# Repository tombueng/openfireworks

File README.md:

<div align="center">

# 🎆 OpenFireworks

**An open, DIY firework show platform — 24-channel ESP32-C3 firing nodes + a browser-based 3D show planner.**

Plan a pyromusical in realistic 3D, then fire it from a cheap, safe, fully open node.

**[▶ Open the interactive 3D viewer](https://tombueng.github.io/openfireworks/)** ·
**[▶ Open OpenFireworks Studio](https://tombueng.github.io/openfireworks/studio/)** — both run in the browser, no install

</div>

> [!WARNING]
> **Pyrotechnics are dangerous and legally regulated.** This repo is an engineering project, not a licence to
> fire. Obey local law and safety distances. On the node the **slide switch is the physical master-off**; firing
> additionally needs an explicit software arm that powers the firing rail (high-side P-FET) and enables the gate
> drivers — boot-safe disarmed by hardware pulldowns.
>
> **Status 2026-11:** the respin-3 hardware is ordered but not yet built or tested; the firmware has never run on
> a board. Do not connect live e-matches before the bench tests in
> [`docs/RESPIN3_BUILD_AND_FIRMWARE.md`](docs/RESPIN3_BUILD_AND_FIRMWARE.md) §5/§6 have passed on your own board.

---

## Gallery

<table>
<tr>
<td width="50%"><br>
<sub><b>The board</b> — 24 channels on 3.5 mm jacks, one RGB status LED per channel</sub></td>
<td width="50%"><br>
<sub><b>Underside</b> — 4 × AA holder, ESP32-C3 SuperMini, master switch</sub></td>
</tr>
<tr>
<td><br>
<sub><b>Case opened</b> — the lid flips off; the board drops into the base</sub></td>
<td><br>
<sub><b>Exploded</b> — base · board · lid with 26 clear window plugs</sub></td>
</tr>
<tr>
<td><br>
<sub><b>Top-down</b> — 74HC595 drivers + 74HC4051 continuity muxes between the jack rows</sub></td>
<td><br>
<sub><b>Opened, from above</b> — board in the base, lid inside-up with its window pockets</sub></td>
</tr>
</table>

All renders come straight from the real KiCad board (its exported 3D model) and the generated enclosure —
Blender/Cycles, script [`enclosure/blender/showcase.py`](enclosure/blender/showcase.py).

### Interactive 3D viewer

Orbit, fly and explode the real board + enclosure in the browser, with the status LEDs lighting through the
windows: **[tombueng.github.io/openfireworks](https://tombueng.github.io/openfireworks/)** (drag the *Open case*
slider).

### Node web UI

Every node serves its own HTTPS web UI (no cloud, no app): all 24 channels with plug detect, continuity and
fire state, live supply voltages, self-test and battery-under-load results, arming, single-channel fire and
cue sequences. Built mobile first for a cold night outside with gloves: big touch targets, STOP as a
full-width bar at the thumb, press-and-hold to fire, a loud "no connection" banner, a high-contrast daylight
theme and the screen kept awake.

*(Screenshot from the UI mock server with simulated data.)*

<br clear="right">

---

## What's here

| Part | Path | Status |
|---|---|---|
| **24-channel firing node v2** (PCB) | `hw/openfireworks_v2.*`, `tools/` | respin 3 done (3 independent review rounds): ERC 0/0, DRC 0 errors / 0 unconnected / parity 0, fab outputs in `export/fab_v2/`, **ordered** |
| **Enclosure** (3D-printed clamshell) | `enclosure/` | generated from the board's 3D models, fit check PASS, interactive three.js viewer; **print package** (multi-material 3MF plates, fit coupon, settings) in `enclosure/print/` |
| **Node firmware** (ESP32-C3) | `firmware/openfireworks_node_v2/` | safe boot, self-tests, arming state machine, per-channel continuity/plug detect, HTTPS web UI, cue sequences, bench tests — compiles clean, **not yet run on hardware** |
| **OpenFireworks Studio** (3D planner/sim/console) | `web/studio/` | self-contained WebGL app: aerial + ground effects, cinematic cameras, sequencer, music, HD/4K recording, demo show |
| **Docs** | `docs/` | design `docs/RESPIN3_DESIGN.md`; assembly, bring-up + firmware safety rules `docs/RESPIN3_BUILD_AND_FIRMWARE.md`; how to regenerate everything `docs/REPRODUCE.md`; BOM with MPNs `export/fab_v2/openfireworks_v2-bom-full.csv` |

This repository holds the result and the scripts that regenerate it. Not in it: datasheets (copyright of
their makers — look them up by the MPN in the BOM), sourcing data, design reviews and older versions.

## What the node measures and records

Everything below is shown live in the node's web UI and on its LEDs. Values marked *expected* are calculated
for respin 3 and still have to be confirmed on the first board.

**Before firing (disarmed, and again on every arm request)**

| what | how | resolution / limit |
|---|---|---|
| Plug in or not, per jack | 100 kΩ plug-detect resistor on the jack's switch contact, read through the mux | yes / no |
| E-match continuity, per jack | test current from 3.3 V through 100 kΩ, 2-level 74HC4051 mux, one ADC | **classes only:** OK (< 0.5 kΩ) / plug with open match / SHORT / no plug, plus the sense voltage. 1–2 Ω cannot be resolved, so a bad but conducting match reads "OK" |
| Battery, resting | VSYS divider on the ADC | V; arming refused below 4.6 V |
| Battery under load | known LED load (~0.3 A) → voltage drop → internal resistance | R_int and the **predicted fire current**; arming refused below 1.2 A |
| Firing rail dead | VFIRE divider, every mux code, with logic lines held high and LED frames running (T0) | rail must read ≈ 0 V |
| Shift-register chain intact | serial readback of the whole chain (T1) | bit-exact |
| Output-enable barrier works | readback pin on the gate drivers' enable (OE_RB), tests T2/T3 | stuck on/off detected |
| Every firing FET switches, none is stuck on | walking-one with the rail off (T5): the commanded channel must read ≈ 1.05 V | per channel |
| Node health | chip temperature, Wi-Fi clients + weakest RSSI, uptime, watchdog, firmware hash | — |

**During a pulse** (one channel at a time, hardware-timed by the RMT peripheral, ≤ 15 ms)

| what | how | effect |
|---|---|---|
| Dead short on the channel | VFIRE (lag-corrected) at 1.5 ms after the start | **abort**: channel off, rail off, logged |
| Bridge burnt through | VSYS sags ≥ 8 % when the match conducts and recovers to ≥ 97 % when it opens | pulse **ends early**; the actual pulse length is recorded |
| Second barrier really switched | OE_RB must go 0 within 10 µs and back to 1 after the pulse | otherwise FAULT |
| Supply collapse | VSYS < 3.5 V for > 2 ms outside a pulse | disarm |

**After firing**

| what | where |
|---|---|
| Per channel: fired, result (ok / short abort / failed), pulse length, time since | channel tile in the web UI; LED dim white = fired, red blink = aborted |
| Continuity after the shot (open = burnt match) | next scan, disarmed |
| Event log: arm/disarm, every pulse with its result, skipped or late cues, faults, refused requests | web UI + USB console, **last 25 events, in RAM only** |

Not recorded: there is no persistent log, no export of a firing report, no time stamp beyond the node's
uptime (no real-time clock; the phone can set a birth time once), and no per-channel current measurement.

## Hardware limits (respin 3)

- **Not tested yet.** The board is ordered, the firmware has never run on it. Everything here is design intent.
- **One channel at a time.** Pulses are sequential (≈ 6.4 ms per channel incl. the LED update); cues must be
  ≥ 20 ms apart. Two effects cannot fire in the very same millisecond on one node.
- **Fire current comes straight from 4 × AA cells** (internal resistance ≈ 0.6–1.2 Ω): enough for standard
  e-matches, not for many in parallel on one channel. Alkaline cells lose a lot in the cold — **use lithium AA
  below 0 °C**. Only AA cells, never 14500 Li-ion (16.8 V destroys the board). Supply range 4.0–7.5 V.
- **Pulse length** ≤ 15 ms (≤ 8 ms when the battery rests below ~5 V, the hold-up must carry the MCU).
- **Jacks:** PJ-320A contacts are rated 0.5 A continuous; the short fire pulses (several A × ms) are fine by
  design but must pass the 50-pulse endurance test (`docs/RESPIN3_BUILD_AND_FIRMWARE.md` §5) before a show.
- **Continuity is a go/no-go test**, not an ohmmeter (see above); a shorted plug pulls the shared rail, so one
  short reads as "short" on every plugged channel and is reported as one fault.
- **Protection:** PPTC (1.5 A hold) on the battery, TVS on every output. The PPTC alone is too slow for a
  sustained short — the firmware's 1.5 ms short abort is the real protection.
- **No hardware arm key.** Both arm barriers are MCU pins with hardware pulldowns; web arming needs a press on
  the module's BOOT button within 30 s. USB is unauthenticated full control — no laptop on the node during a show.
- **Radio:** one node, its own hidden Wi-Fi access point (2.4 GHz, external antenna), range of a phone hotspot.
  No multi-node link, no time sync between nodes, no LoRa yet.
- **Cue lists live in RAM** (≤ 3600 s, lost on reset); the node auto-disarms after 30 min armed.
- **Weather:** the printed case is splash-resistant at best and the jacks are open. Dew: consider conformal
  coating on the bottom side for night shows.
- **No 5 V LED-rail sense** (the UI shows an estimate); LED current is capped at 0.3 A.

## The hardware node

**One board, 100 × 100 mm, 4 layers (JLCPCB standard stack-up).**

- 🧠 **ESP32-C3 SuperMini** (USB-C for programming only) · 4 × 74HC595 + 4 × 74HC4051
- 🔌 **24 low-side N-FET channels** (AO3400) on **3.5 mm jacks** (PJ-320A, with plug detect)
- 🔋 **4 × AA cells** in an on-board Keystone 2477 holder (alkaline, NiMH or lithium, 4.0–7.5 V) ·
  reverse-polarity P-FET · **PPTC** · slide switch master-off · e-matches fire straight from the cells through
  the channel FET; LDOs for 3.3 V (with hold-up capacitors) and the 5 V LED rail
- 🛡️ **Software arm with two independent barriers**, each on its own MCU pin with its own pulldown: ARM P-FET on
  the firing rail (bled to 0 V when disarmed) + gate-driver output enable (with readback); VFIRE and VBAT
  sensed by the ADC; per-channel continuity through a 2-level mux; ESD TVS on every output
- 🌈 **26 WS2812B status LEDs** (one per channel + 2 heads) on a 5 V LDO rail with a level shifter; any subset
  of channels can be populated (per-channel LED bypass jumper)
- 📡 External 2.4 GHz antenna through the enclosure wall (U.FL → SMA pigtail)
- ♻️ **Reproducible:** schematic, board, routing helpers, fab outputs, enclosure, print plates and renders are
  all generated by scripts — pipeline in [`docs/REPRODUCE.md`](docs/REPRODUCE.md)

## Enclosure

A two-part snap-fit clamshell (PETG), generated with build123d from the board's own 3D model: jack half-holes
in both halves, 26 frosted clear window plugs printed with the second extruder **beside** the lid, print-in-place
release buttons, SMA antenna port. Printing: [`enclosure/print/PRINT_SETTINGS.md`](enclosure/print/PRINT_SETTINGS.md)
(start with the fit coupon on plate 0).

## Firmware

```bash
firmware/build.sh          # bring-up
firmware/build.sh show     # show firmware
firmware/build.sh bench    # bench tests
```

See [`firmware/openfireworks_node_v2/README.md`](firmware/openfireworks_node_v2/README.md) for the safety model, the
LED colour code and the web UI.

## OpenFireworks Studio

Open `web/studio/index.html` in a modern browser (needs WebGL; three.js loads from jsDelivr), or use the hosted
copy: **[tombueng.github.io/openfireworks/studio](https://tombueng.github.io/openfireworks/studio/)**

- ▶ Show runs the demo; add effects from the library at the playhead; drag = orbit, scroll = zoom
- Cameras incl. **drone fly-through**; an **auto-director** cuts between them
- Wind drifts smoke + stars; load your own music; **record HD/4K** to a `.webm` (local only)
- Export/import shows as JSON

## Roadmap (honest)

Rig/box modelling + igniter-port mapping UI + printable setup sheets · browser-DB versioned save · monitoring
console UI + fleet management · production crypto (HMAC/AEAD) · LoRa second radio · product catalog import ·
firing-system export adapters.

## License

MIT — see [`LICENSE`](LICENSE). It covers everything in this repository: software, firmware, hardware design
files (schematic, board, fab outputs), enclosure and documentation. Third-party parts (KiCad library footprints
and 3D models, makers' datasheets, three.js loaded from a CDN) keep their own licenses.

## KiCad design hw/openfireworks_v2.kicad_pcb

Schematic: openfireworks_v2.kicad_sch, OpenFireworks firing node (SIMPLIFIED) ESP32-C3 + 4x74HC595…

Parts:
A1: ESP32-C3 SuperMini; ESP32C3_SuperMini_MINIV1; MPN ESP32-C3 SuperMini 'ESP32-C3 MINI V1' (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
BT1: 4xAA holder; BatteryHolder_Keystone_2477_4xAA; MPN Keystone 2477 (PC battery holder 4 x AA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
C1, C2, C4, C5, C7, C66: 10uF; C_0805_2012Metric; MPN 10uF 25V X5R 0805
C3, C6, C8, C10, C11, C12, C13, C14, C15, C16, C17, C18, C19, C20, C21, C22, C23, C24, C65, C71, C72, C73, C74, C75, C76: 100nF; C_0603_1608Metric; MPN 100nF 50V X7R 0603
C9, C60, C61, C70: 10nF; C_0603_1608Metric; MPN 10nF 50V X7R 0603
C62, C63, C64: 10uF; C_1206_3216Metric; MPN Samsung CL31B106KAHNNNF (10uF 25V X7R 1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
C67, C68: 470uF 10V; CP_Radial_D8.0mm_P3.50mm; MPN Nichicon UPW1A471MPD (470 uF 10 V, low 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
C69: 220nF; C_0603_1608Metric; MPN 220nF 25V X7R 0603
D1, D2, D3, D4, D5, D6, D7, D8, D9, D10, D11, D12, D13, D14, D15, D16, D17, D18, D19, D20, D21, D22, D23, D24, D49, D50: WS2812B; LED_WS2812B_PLCC4_5.0x5.0mm_P3.2mm; MPN WS2812B 5050 PLCC4 addressable RGB (5 V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
D25, D26, D27, D28, D29, D30, D31, D32, D33, D34, D35, D36, D37, D38, D39, D40, D41, D42, D43, D44, D45, D46, D47, D48, D52: ESD5Z12-AQ; D_SOD-523; MPN Diotec ESD5Z12-AQ (unidirectional ESD T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
D51: 1N5819HW; D_SOD-123; MPN Diodes Inc 1N5819HW-7-F (Schottky 40 V 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
F1: PPTC 1.5A hold; Fuse_2920_7451Metric_Pad2.10x5.45mm_HandSolder; MPN Littelfuse 2920L150DR (PPTC 1.5 A hold,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
J1, J2, J3, J4, J5, J6, J7, J8, J9, J10, J11, J12, J13, J14, J15, J16, J17, J18, J19, J20, J21, J22, J23, J24: PJ-320A; Jack_35mm_PJ320A_THT; MPN PJ-320A 3.5 mm 4-pole jack, THT 4-pin, 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
JP1: JP_D0; SolderJumper-2_P1.3mm_Open_Pad1.0x1.5mm; MPN solder bridge (PCB copper, no bought pa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
JP2: JP_D1; SolderJumper-2_P1.3mm_Open_Pad1.0x1.5mm; MPN solder bridge (PCB copper, no bought pa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
JP3: JP_D2; SolderJumper-2_P1.3mm_Open_Pad1.0x1.5mm; MPN solder bridge (PCB copper, no bought pa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
JP4: JP_D3; SolderJumper-2_P1.3mm_Open_Pad1.0x1.5mm; MPN solder bridge (PCB copper, no bought pa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
JP5: JP_D4; SolderJumper-2_P1.3mm_Open_Pad1.0x1.5mm; MPN solder bridge (PCB copper, no bought pa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
JP6: JP_D5; SolderJumper-2_P1.3mm_Open_Pad1.0x1.5mm; MPN solder bridge (PCB copper, no bought pa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
JP7: JP_D6; SolderJumper-2_P1.3mm_Open_Pad1.0x1.5mm; MPN solder bridge (PCB copper, no bought pa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
JP8: JP_D7; SolderJumper-2_P1.3mm_Open_Pad1.0x1.5mm; MPN solder bridge (PCB copper, no bought pa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
JP9: JP_D8; SolderJumper-2_P1.3mm_Open_Pad1.0x1.5mm; MPN solder bridge (PCB copper, no bought pa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
JP10: JP_D9; SolderJumper-2_P1.3mm_Open_Pad1.0x1.5mm; MPN solder bridge (PCB copper, no bought pa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
JP11: JP_D10; SolderJumper-2_P1.3mm_Open_Pad1.0x1.5mm; MPN solder bridge (PCB copper, no bought pa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
JP12: JP_D11; SolderJumper-2_P1.3mm_Open_Pad1.0x1.5mm; MPN solder bridge (PCB copper, no bought pa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
JP13: JP_D12; SolderJumper-2_P1.3mm_Open_Pad1.0x1.5mm; MPN solder bridge (PCB copper, no bought pa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
JP14: JP_D13; SolderJumper-2_P1.3mm_Open_Pad1.0x1.5mm; MPN solder bridge (PCB copper, no bought pa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
JP15: JP_D14; SolderJumper-2_P1.3mm_Open_Pad1.0x1.5mm; MPN solder bridge (PCB copper, no bought pa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
JP16: JP_D15; SolderJumper-2_P1.3mm_Open_Pad1.0x1.5mm; MPN solder bridge (PCB copper, no bought pa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
JP17: JP_D16; SolderJumper-2_P1.3mm_Open_Pad1.0x1.5mm; MPN solder bridge (PCB copper, no bought pa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
JP18: JP_D17; SolderJumper-2_P1.3mm_Open_Pad1.0x1.5mm; MPN solder bridge (PCB copper, no bought pa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
JP19: JP_D18; SolderJumper-2_P1.3mm_Open_Pad1.0x1.5mm; MPN solder bridge (PCB copper, no bought pa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
JP20: JP_D19; SolderJumper-2_P1.3mm_Open_Pad1.0x1.5mm; MPN solder bridge (PCB copper, no bought pa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
JP21: JP_D20; SolderJumper-2_P1.3mm_Open_Pad1.0x1.5mm; MPN solder bridge (PCB copper, no bought pa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
JP22: JP_D21; SolderJumper-2_P1.3mm_Open_Pad1.0x1.5mm; MPN solder bridge (PCB copper, no bought pa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
JP23: JP_D22; SolderJumper-2_P1.3mm_Open_Pad1.0x1.5mm; MPN solder bridge (PCB copper, no bought pa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
JP24: JP_D23; SolderJumper-2_P1.3mm_Open_Pad1.0x1.5mm; MPN solder bridge (PCB copper, no bought pa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
Q1, Q2, Q3, Q4, Q5, Q6, Q7, Q8, Q9, Q10, Q11, Q12, Q13, Q14, Q15, Q16, Q17, Q18, Q19, Q20, Q21, Q22, Q23, Q24: AO3400 (low-side); SOT-23; MPN AO3400 class N-FET, SOT-23 G1/S2/D3: AO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
Q25, Q26: AO3400 (arm driver); SOT-23; MPN AO3400 class N-FET, SOT-23 G1/S2/D3 (sa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
Q27: DMP2035UVT (ARM rail); TSOT-23-6; MPN Diodes DMP2035UVT-7 (P-FET -20 V, VGS +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
Q28: DMP2035UVT (reverse block); TSOT-23-6; MPN Diodes DMP2035UVT-7 (P-FET -20 V, VGS +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
R1, R4, R13, R14, R15, R182, R183, R184, R185, R186: 10k; R_0603_1608Metric; MPN any 10k 0603 1%
R2, R19, R22, R25, R28, R31, R34, R37, R40, R43, R46, R49, R52, R55, R58, R61, R64, R67, R70, R73, R76, R79, R82, R85, R88: 47k; R_0603_1608Metric; MPN any 47k 0603 1%
R3, R5: 2.2k; R_0603_1608Metric; MPN any 2.2k 0603 1%
R6, R8: 220k; R_0603_1608Metric; MPN any 220k 0603 1%
R7, R9, R16, R18, R21, R24, R27, R30, R33, R36, R39, R42, R45, R48, R51, R54, R57, R60, R63, R66, R69, R72, R75, R78, R81, R84, R87, R150, R151, R152, R153, R154, R155, R156, R157, R158, R159, R160, R161, R162, R163, R164, R165, R166, R167, R168, R169, R170, R171, R172, R173, R181: 100k; R_0603_1608Metric; MPN any 100k 0603 1%
R10, R11, R12, R180: 33R; R_0603_1608Metric; MPN any 33R 0603
R17, R20, R23, R26, R29, R32, R35, R38, R41, R44, R47, R50, R53, R56, R59, R62, R65, R68, R71, R74, R77, R80, R83, R86: 150R; R_0603_1608Metric; MPN any 150R 0603
R187: 1k; R_0603_1608Metric; MPN any 1k 0603 1%
SW1: 5MS1S102AM6QE; Switch_Slide_LightCountry_5MS1_M6; MPN Light Country 5MS1S102AM6QE (SPDT ON-ON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
TP1: VSYS; TestPoint_Pad_D1.0mm; MPN test pad (PCB copper)
TP2: GND; TestPoint_Pad_D1.0mm; MPN test pad (PCB copper)
TP3: 3V3; TestPoint_Pad_D1.0mm; MPN test pad (PCB copper)
TP4: GND2; TestPoint_Pad_D1.0mm; MPN test pad (PCB copper)
TP5: GATE_OE_N; TestPoint_Pad_D1.0mm; MPN test pad (PCB copper)
TP6: GND3; TestPoint_Pad_D1.0mm; MPN test pad (PCB copper)
TP7: VBAT_DIV; TestPoint_Pad_D1.0mm; MPN test pad (PCB copper)
TP8: MUX_ADC; TestPoint_Pad_D1.0mm; MPN test pad (PCB copper)
TP9: MOSI; TestPoint_Pad_D1.0mm; MPN test pad (PCB copper)
TP10: SCK; TestPoint_Pad_D1.0mm; MPN test pad (PCB copper)
TP11: RCLK; TestPoint_Pad_D1.0mm; MPN test pad (PCB copper)
TP12: RGB_DATA; TestPoint_Pad_D1.0mm; MPN test pad (PCB copper)
TP13: VFIRE; TestPoint_Pad_D1.0mm; MPN test pad (PCB copper)
TP14: V5_LED; TestPoint_Pad_D1.0mm; MPN test pad (PCB copper)
TP15: VLDO; TestPoint_Pad_D1.0mm; MPN test pad (PCB copper)
U1, U2, U3, U4: 74HC595; SOIC-16_3.9x9.9mm_P1.27mm; MPN SN74HC595D (8-bit shift register, SOIC-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
U5, U6, U7, U8: 74HC4051D; SOIC-16_3.9x9.9mm_P1.27mm; MPN Toshiba 74HC4051D(BJ) (8:1 analog mux, 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
U9: LP38692MP-3.3; SOT-223-5; MPN TI LP38692MP-3.3/NOPB (1 A LDO, VIN 2.7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
U10: SN74LV1T125DCKR; SOT-353_SC-70-5; MPN TI SN74LV1T125DCKR (single buffer with 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
U11: LP38691DTX-5.0; TO-252-2; MPN TI LP38691DTX-5.0/NOPB (500 mA LDO, VIN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

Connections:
+3V3: A1.2, C2.1, C3.1, C7.1, C8.1, C10.1, C11.1, C12.1, C13.1, C14.1, C15.1, C16.1, C17.1, R4.1, R16.1, R182.1, R183.1, R184.1, TP3.1, U1.10 (~SRCLR), U1.16 (VCC), U2.10 (~SRCLR), U2.16 (VCC), U3.10 (~SRCLR), U3.16 (VCC), U4.10 (~SRCLR), U4.16 (VCC), U5.16 (VDD), U6.16 (VDD), U7.16 (VDD), U8.16 (VDD), U9.3 (OUT)
/ARM_GATE: C69.2, C70.1, Q27.3 (G), R1.2, R187.1
/ARM_PD: Q25.3 (D), R187.2
/BAT_P: BT1.1, Q28.1 (D), Q28.2 (D), Q28.5 (D), Q28.6 (D)
/BAT_PF: F1.2, Q28.4 (S)
/BAT_SW: F1.1, SW1.2 (B)
/CH0: D25.1 (K), J1.T, Q1.3 (D), R19.1, R150.2
/CH1: D26.1 (K), J2.T, Q2.3 (D), R22.1, R151.2
/CH2: D27.1 (K), J3.T, Q3.3 (D), R25.1, R152.2
/CH3: D28.1 (K), J4.T, Q4.3 (D), R28.1, R153.2
/CH4: D29.1 (K), J5.T, Q5.3 (D), R31.1, R154.2
/CH5: D30.1 (K), J6.T, Q6.3 (D), R34.1, R155.2
/CH6: D31.1 (K), J7.T, Q7.3 (D), R37.1, R156.2
/CH7: D32.1 (K), J8.T, Q8.3 (D), R40.1, R157.2
/CH8: D33.1 (K), J9.T, Q9.3 (D), R43.1, R158.2
/CH9: D34.1 (K), J10.T, Q10.3 (D), R46.1, R159.2
/CH10: D35.1 (K), J11.T, Q11.3 (D), R49.1, R160.2
/CH11: D36.1 (K), J12.T, Q12.3 (D), R52.1, R161.2
/CH12: D37.1 (K), J13.T, Q13.3 (D), R55.1, R162.2
/CH13: D38.1 (K), J14.T, Q14.3 (D), R58.1, R163.2
/CH14: D39.1 (K), J15.T, Q15.3 (D), R61.1, R164.2
/CH15: D40.1 (K), J16.T, Q16.3 (D), R64.1, R165.2
/CH16: D41.1 (K), J17.T, Q17.3 (D), R67.1, R166.2
/CH17: D42.1 (K), J18.T, Q18.3 (D), R70.1, R167.2
/CH18: D43.1 (K), J19.T, Q19.3 (D), R73.1, R168.2
/CH19: D44.1 (K), J20.T, Q20.3 (D), R76.1, R169.2
/CH20: D45.1 (K), J21.T, Q21.3 (D), R79.1, R170.2
/CH21: D46.1 (K), J22.T, Q22.3 (D), R82.1, R171.2
/CH22: D47.1 (K), J23.T, Q23.3 (D), R85.1, R172.2
/CH23: D48.1 (K), J24.T, Q24.3 (D), R88.1, R173.2
/FW_ARM: A1.12, Q25.1 (G), R5.1
/FW_OE: A1.6, Q26.1 (G), R3.1
/GATE0: Q1.1 (G), R17.2, R18.1
/GATE1: Q2.1 (G), R20.2, R21.1
/GATE2: Q3.1 (G), R23.2, R24.1
/GATE3: Q4.1 (G), R26.2, R27.1
/GATE4: Q5.1 (G), R29.2, R30.1
/GATE5: Q6.1 (G), R32.2, R33.1
/GATE6: Q7.1 (G), R35.2, R36.1
/GATE7: Q8.1 (G), R38.2, R39.1
/GATE8: Q9.1 (G), R41.2, R42.1
/GATE9: Q10.1 (G), R44.2, R45.1
/GATE10: Q11.1 (G), R47.2, R48.1
/GATE11: Q12.1 (G), R50.2, R51.1
/GATE12: Q13.1 (G), R53.2, R54.1
/GATE13: Q14.1 (G), R56.2, R57.1
/GATE14: Q15.1 (G), R59.2, R60.1
/GATE15: Q16.1 (G), R62.2, R63.1
/GATE16: Q17.1 (G), R65.2, R66.1
/GATE17: Q18.1 (G), R68.2, R69.1
/GATE18: Q19.1 (G), R71.2, R72.1
/GATE19: Q20.1 (G), R74.2, R75.1
/GATE20: Q21.1 (G), R77.2, R78.1
/GATE21: Q22.1 (G), R80.2, R81.1
/GATE22: Q23.1 (G), R83.2, R84.1
/GATE23: Q24.1 (G), R86.2, R87.1
/GATE_OE_N: Q26.3 (D), R4.2, R182.2, R183.2, R184.2, R185.1, TP5.1, U2.13 (~OE), U3.13 (~OE), U4.13 (~OE)
/JDET0: J1.R2, R150.1
/JDET1: J2.R2, R151.1
/JDET2: J3.R2, R152.1
/JDET3: J4.R2, R153.1
/JDET4: J5.R2, R154.1
/JDET5: J6.R2, R155.1
/JDET6: J7.R2, R156.1
/JDET7: J8.R2, R157.1
/JDET8: J9.R2, R158.1
/JDET9: J10.R2, R159.1
/JDET10: J11.R2, R160.1
/JDET11: J12.R2, R161.1
/JDET12: J13.R2, R162.1
/JDET13: J14.R2, R163.1
/JDET14: J15.R2, R164.1
/JDET15: J16.R2, R165.1
/JDET16: J17.R2, R166.1
/JDET17: J18.R2, R167.1
/JDET18: J19.R2, R168.1
/JDET19: J20.R2, R169.1
/JDET20: J21.R2, R170.1
/JDET21: J22.R2, R171.1
/JDET22: J23.R2, R172.1
/JDET23: J24.R2, R173.1
/MOSI: R11.2, R186.1, TP9.1, U1.14 (SER)
/MOSI_M: A1.9, R11.1
/MUXC_A: U5.3 (X), U8.13 (X0)
/MUXC_B: U6.3 (X), U8.14 (X1)
/MUXC_C: U7.3 (X), U8.15 (X2)
/MUXIN0: R19.2, U5.13 (X0)
/MUXIN1: R22.2, U5.14 (X1)
/MUXIN2: R25.2, U5.15 (X2)
/MUXIN3: R28.2, U5.12 (X3)
/MUXIN4: R31.2, U5.1 (X4)
/MUXIN5: R34.2, U5.5 (X5)
/MUXIN6: R37.2, U5.2 (X6)
/MUXIN7: R40.2, U5.4 (X7)
/MUXIN8: R43.2, U6.13 (X0)
/MUXIN9: R46.2, U6.14 (X1)
/MUXIN10: R49.2, U6.15 (X2)
/MUXIN11: R52.2, U6.12 (X3)
/MUXIN12: R55.2, U6.1 (X4)
/MUXIN13: R58.2, U6.5 (X5)
/MUXIN14: R61.2, U6.2 (X6)
/MUXIN15: R64.2, U6.4 (X7)
/MUXIN16: R67.2, U7.13 (X0)
/MUXIN17: R70.2, U7.14 (X1)
/MUXIN18: R73.2, U7.15 (X2)
/MUXIN19: R76.2, U7.12 (X3)
/MUXIN20: R79.2, U7.1 (X4)
/MUXIN21: R82.2, U7.5 (X5)
/MUXIN22: R85.2, U7.2 (X6)
/MUXIN23: R88.2, U7.4 (X7)
/MUX_ADC: A1.4, C9.1, R16.2, TP8.1, U8.3 (X)
/OE_RB: A1.13, R185.2
/RCLK: R12.2, R14.1, TP11.1, U1.12 (RCLK), U2.12 (RCLK), U3.12 (RCLK), U4.12 (RCLK)
/RCLK_M: A1.10, R12.1
/RGBD0: D1.2 (DOUT), D2.4 (DIN), JP1.2 (B), JP2.1 (A)
/RGBD1: D2.2 (DOUT), D3.4 (DIN), JP2.2 (B), JP3.1 (A)
/RGBD2: D3.2 (DOUT), D4.4 (DIN), JP3.2 (B), JP4.1 (A)
/RGBD3: D4.2 (DOUT), D5.4 (DIN), JP4.2 (B), JP5.1 (A)
/RGBD4: D5.2 (DOUT), D6.4 (DIN), JP5.2 (B), JP6.1 (A)
/RGBD5: D6.2 (DOUT), D7.4 (DIN), JP6.2 (B), JP7.1 (A)
/RGBD6: D7.2 (DOUT), D8.4 (DIN), JP7.2 (B), JP8.1 (A)
/RGBD7: D8.2 (DOUT), D9.4 (DIN), JP8.2 (B), JP9.1 (A)
/RGBD8: D9.2 (DOUT), D10.4 (DIN), JP9.2 (B), JP10.1 (A)
/RGBD9: D10.2 (DOUT), D11.4 (DIN), JP10.2 (B), JP11.1 (A)
/RGBD10: D11.2 (DOUT), D12.4 (DIN), JP11.2 (B), JP12.1 (A)
/RGBD11: D12.2 (DOUT), D13.4 (DIN), JP12.2 (B), JP13.1 (A)
/RGBD12: D13.2 (DOUT), D14.4 (DIN), JP13.2 (B), JP14.1 (A)
/RGBD13: D14.2 (DOUT), D15.4 (DIN), JP14.2 (B), JP15.1 (A)
/RGBD14: D15.2 (DOUT), D16.4 (DIN), JP15.2 (B), JP16.1 (A)
/RGBD15: D16.2 (DOUT), D17.4 (DIN), JP16.2 (B), JP17.1 (A)
/RGBD16: D17.2 (DOUT), D18.4 (DIN), JP17.2 (B), JP18.1 (A)
/RGBD17: D18.2 (DOUT), D19.4 (DIN), JP18.2 (B), JP19.1 (A)
/RGBD18: D19.2 (DOUT), D20.4 (DIN), JP19.2 (B), JP20.1 (A)
/RGBD19: D20.2 (DOUT), D21.4 (DIN), JP20.2 (B), JP21.1 (A)
/RGBD20: D21.2 (DOUT), D22.4 (DIN), JP21.2 (B), JP22.1 (A)
/RGBD21: D22.2 (DOUT), D23.4 (DIN), JP22.2 (B), JP23.1 (A)
/RGBD22: D23.2 (DOUT), D24.4 (DIN), JP23.2 (B), JP24.1 (A)
/RGBD23: D24.2 (DOUT), JP24.2 (B)
/RGB_5V: D49.4 (DIN), R180.2
/RGB_5VR: R180.1, U10.4
/RGB_DATA: A1.11, R181.1, TP12.1, U10.2
/RGB_IN: D1.4 (DIN), D50.2 (DOUT), JP1.1 (A)
/RGB_MID: D49.2 (DOUT), D50.4 (DIN)
/SCK: R10.2, R13.1, TP10.1, U1.11 (SRCLK), U2.11 (SRCLK), U3.11 (SRCLK), U4.11 (SRCLK)
/SCK_M: A1.8, R10.1
/SELH_A: U1.3 (QD), U8.11 (A)
/SELH_B: U1.4 (QE), U8.10 (B)
/SELH_C: U1.5 (QF), U8.9 (C)
/SEL_A: U1.15 (QA), U5.11 (A), U6.11 (A), U7.11 (A)
/SEL_B: U1.1 (QB), U5.10 (B), U6.10 (B), U7.10 (B)
/SEL_C: U1.2 (QC), U5.9 (C), U6.9 (C), U7.9 (C)
/SER1: U1.9 (QH'), U2.14 (SER)
/SER2: U2.9 (QH'), U3.14 (SER)
/SER3: U3.9 (QH'), U4.14 (SER)
/SRGATE0: R17.1, U2.15 (QA)
/SRGATE1: R20.1, U2.1 (QB)
/SRGATE2: R23.1, U2.2 (QC)
/SRGATE3: R26.1, U2.3 (QD)
/SRGATE4: R29.1, U2.4 (QE)
/SRGATE5: R32.1, U2.5 (QF)
/SRGATE6: R35.1, U2.6 (QG)
/SRGATE7: R38.1, U2.7 (QH)
/SRGATE8: R41.1, U3.15 (QA)
/SRGATE9: R44.1, U3.1 (QB)
/SRGATE10: R47.1, U3.2 (QC)
/SRGATE11: R50.1, U3.3 (QD)
/SRGATE12: R53.1, U3.4 (QE)
/SRGATE13: R56.1, U3.5 (QF)
/SRGATE14: R59.1, U3.6 (QG)
/SRGATE15: R62.1, U3.7 (QH)
/SRGATE16: R65.1, U4.15 (QA)
/SRGATE17: R68.1, U4.1 (QB)
/SRGATE18: R71.1, U4.2 (QC)
/SRGATE19: R74.1, U4.3 (QD)
/SRGATE20: R77.1, U4.4 (QE)
/SRGATE21: R80.1, U4.5 (QF)
/SRGATE22: R83.1, U4.6 (QG)
/SRGATE23: R86.1, U4.7 (QH)
/SR_QH: R15.1, U4.9 (QH')
/SR_RB: A1.16, R15.2
/V5_LED: C18.1, C19.1, C20.1, C21.1, C22.1, C23.1, C24.1, C63.1, C64.1, C65.1, C71.1, C72.1, C73.1, C74.1, C75.1, C76.1, D1.1 (VDD), D2.1 (VDD), D3.1 (VDD), D4.1 (VDD), D5.1 (VDD), D6.1 (VDD), D7.1 (VDD), D8.1 (VDD), D9.1 (VDD), D10.1 (VDD), D11.1 (VDD), D12.1 (VDD), D13.1 (VDD), D14.1 (VDD), D15.1 (VDD), D16.1 (VDD), D17.1 (VDD), D18.1 (VDD), D19.1 (VDD), D20.1 (VDD), D21.1 (VDD), D22.1 (VDD), D23.1 (VDD), D24.1 (VDD), D49.1 (VDD), D50.1 (VDD), TP14.1, U10.5 (VCC), U11.1 (OUT)
/VBAT_DIV: A1.5, C60.1, R6.2, R7.1, TP7.1
/VFIRE: C70.2, D52.1 (K), J1.R1, J1.S, J2.R1, J2.S, J3.R1, J3.S, J4.R1, J4.S, J5.R1, J5.S, J6.R1, J6.S, J7.R1, J7.S, J8.R1, J8.S, J9.R1, J9.S, J10.R1, J10.S, J11.R1, J11.S, J12.R1, J12.S, J13.R1, J13.S, J14.R1, J14.S, J15.R1, J15.S, J16.R1, J16.S, J17.R1, J17.S, J18.R1, J18.S, J19.R1, J19.S, J20.R1, J20.S, J21.R1, J21.S, J22.R1, J22.S, J23.R1, J23.S, J24.R1, J24.S, Q27.1 (D), Q27.2 (D), Q27.5 (D), Q27.6 (D), R2.1, R8.1, TP13.1
/VFIRE_SNS: A1.7, C61.1, R8.2, R9.1
/VLDO: C66.1, C67.1, C68.1, D51.1 (K), TP15.1, U9.1 (EN), U9.4 (IN)
/VSYS: C1.1, C4.1, C5.1, C6.1, C62.1, C69.1, D51.2 (A), Q27.4 (S), R1.1, R6.1, SW1.1 (A), TP1.1, U11.3 (IN)
GND: A1.3, BT1.2, C1.2, C2.2, C3.2, C4.2, C5.2, C6.2, C7.2, C8.2, C9.2, C10.2, C11.2, C12.2, C13.2, C14.2, C15.2, C16.2, C17.2, C18.2, C19.2, C20.2, C21.2, C22.2, C23.2, C24.2, C60.2, C61.2, C62.2, C63.2, C64.2, C65.2, C66.2, C67.2, C68.2, C71.2, C72.2, C73.2, C74.2, C75.2, C76.2, D1.3 (VSS), D2.3 (VSS), D3.3 (VSS), D4.3 (VSS), D5.3 (VSS), D6.3 (VSS), D7.3 (VSS), D8.3 (VSS), D9.3 (VSS), D10.3 (VSS), D11.3 (VSS), D12.3 (VSS), D13.3 (VSS), D14.3 (VSS), D15.3 (VSS), D16.3 (VSS), D17.3 (VSS), D18.3 (VSS), D19.3 (VSS), D20.3 (VSS), D21.3 (VSS), D22.3 (VSS), D23.3 (VSS), D24.3 (VSS), D25.2 (A), D26.2 (A), D27.2 (A), D28.2 (A), D29.2 (A), D30.2 (A), D31.2 (A), D32.2 (A), D33.2 (A), D34.2 (A), D35.2 (A), D36.2 (A), D37.2 (A), D38.2 (A), D39.2 (A), D40.2 (A), D41.2 (A), D42.2 (A), D43.2 (A), D44.2 (A), D45.2 (A), D46.2 (A), D47.2 (A), D48.2 (A), D49.3 (VSS), D50.3 (VSS), D52.2 (A), Q1.2 (S), Q2.2 (S), Q3.2 (S), Q4.2 (S), Q5.2 (S), Q6.2 (S), Q7.2 (S), Q8.2 (S), Q9.2 (S), Q10.2 (S), Q11.2 (S), Q12.2 (S), Q13.2 (S), Q14.2 (S), Q15.2 (S), Q16.2 (S), Q17.2 (S), Q18.2 (S), Q19.2 (S), Q20.2 (S), Q21.2 (S), Q22.2 (S), Q23.2 (S), Q24.2 (S), Q25.2 (S), Q26.2 (S), Q28.3 (G), R2.2, R3.2, R5.2, R7.2, R9.2, R13.2, R14.2, R18.2, R21.2, R24.2, R27.2, R30.2, R33.2, R36.2, R39.2, R42.2, R45.2, R48.2, R51.2, R54.2, R57.2, R60.2, R63.2, R66.2, R69.2, R72.2, R75.2, R78.2, R81.2, R84.2, R87.2, R181.2, R186.2, TP2.1, TP4.1, TP6.1, U1.8 (GND), U1.13 (~OE), U2.8 (GND), U3.8 (GND), U4.8 (GND), U5.6 (INH), U5.7 (VEE), U5.8 (VSS), U6.6 (INH), U6.7 (VEE), U6.8 (VSS), U7.6 (INH), U7.7 (VEE), U7.8 (VSS), U8.6 (INH), U8.7 (VEE), U8.8 (VSS), U9.5 (GND), U10.1, U10.3 (GND), U11.2 (GND)

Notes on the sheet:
POWER / SOFTWARE ARM (4 x AA holder -> reverse-block P-FET -> PPTC -> slide switch ON/OFF -> VSYS ; D51 + hold-up -> LDO 3V3 ; ARM = high-side P-FET VSYS->VFIRE (rail dead when disarmed))
BT1: 4 x AA (alkaline / NiMH / lithium, 4.0-7.5 V) in a Keystone 2477 holder, TOP side, silk +/-
Q28 reverse-battery block (fitted): cells inserted the wrong way -> off, nothing behind it sees a negative voltage.
F1: PPTC 1.5 A hold (passes the fire pulse; overload / VSYS-short protection only)
SW1: slide switch ON/OFF (north edge, next to the C3 USB-C) = master off
U9 LP38692MP-3.3: VSYS -> D51 -> VLDO (C67+C68 2x470 uF hold-up) -> 3V3 (feeds the SuperMini 3V3 pin; its 5V pin is open).
D51: a fire pulse sags VSYS, VLDO keeps its charge; USB in + SW1 OFF -> the module LDO powers +3V3, VSYS stays dead.
VSYS bulk 2x10uF+100nF (the cells supply the fire pulse; C67/C68 behind D51 carry the MCU through it).
SOFTWARE ARM: Q27 (HIGH-SIDE P-FET VSYS->VFIRE) switches the WHOLE firing rail. DISARMED -> Q27 off + 47k bleed -> VFIRE DEAD. (Armed state is shown by firmware on a WS2812.)
TWO independent barriers: FW_ARM (GPIO20) -> Q25 -> Q27 rail; FW_OE (GPIO4) -> Q26 -> 595 outputs. Each has its own 2.2k pulldown: one open resistor or one short opens only ONE barrier. Arm edge slowed by R187 1k + C70 10nF (Miller).
VBAT divider 220k:100k (7.5 V -> 2.34 V at GPIO1) + 10 nF at the ADC pin
VFIRE sense divider 220k:100k (-> GPIO3 ADC) + 10 nF: detects a hot rail
MCU (ESP32-C3 SuperMini MINI V1 - 3V3 pin fed directly, 5V pin open; USB-C at the north edge by SW1 = programming only)
Pin map (pad:GPIO:signal):
4:GPIO0:MUX_ADC 5:GPIO1:VBAT_DIV 7:GPIO3:VFIRE_SNS 8:GPIO5:SCK 9:GPIO6:MOSI 10:GPIO7:RCLK
11:GPIO10:RGB_DATA 12:GPIO20:FW_ARM 6:GPIO4:FW_OE 16:GPIO21:SR_RB (1:5V open, 2:3V3, 3:GND)
13:GPIO2*:OE_RB (GATE_OE_N readback via 10k) unused NC: 14:GPIO8* 15:GPIO9* (* strapping)
3V3 bulk + decoupling (at the module's 3V3/GND pads)
33R series at the module (long SPI lines), 10k pulldowns on SCK/RCLK/MOSI, U4 QH' -> 10k -> GPIO21 (firmware verifies the chain before arming), 10 nF at MUX_ADC.
SHIFT CHAIN (U1 = control 74HC595 [mux select, ~OE=GND] + U2/U3/U4 = 3x gate-driver 74HC595 [24 gates, ~OE=GATE_OE_N, ARM-gated]) - all plain 74HC @ +3V3
Chain MOSI->U1->U2->U3->U4 (QH'->SER via SER1/2/3); SCK/RCLK shared; ~SRCLR=+3V3. U1 ~OE=GND (always on); U2/U3/U4 ~OE=GATE_OE_N (ARM-gated).
CONTINUITY MUX (U5/U6/U7 = 8 CHn each ; U8 = level 2: the 3 commons -> ONE slow ADC. Test current ~16 uA from +3V3 through an intact e-match (reads low); open reads high via R_test.)
U8 level 2: X0-2 = commons -> MUX_ADC (GPIO0). R_test 100k +3V3->MUX_ADC (continuity DISARMED, return path via the dead VFIRE rail). Select SELH_*. No-fire current.
CHANNEL x24 - CH0...CH23 (one identical block per channel: 3.5 mm jack + plug-detect 100k + low-side N-FET + gate series 150R + gate pulldown 100k + continuity tap 47k + RGB LED with DIN->DOUT bypass + ESD TVS)
x24 - CH0...CH23. Fire: VFIRE (sleeve + R1, ARM-gated) -> e-match -> CHn (tip = FET drain) -> FET -> GND. Gate: SRGATEn -150R-> GATEn -> FET gate (100k pulldown). Continuity: CHn -47k-> MUXINn -> CD4051; plug detect: R2 -100k-> CHn. RGB chain DIN->DOUT (bypass JPn for unpopulated channels). ESD TVS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
CH0
CH1
CH2
CH3
CH4
CH5
CH6
CH7
CH8
CH9
CH10
CH11
CH12
CH13
CH14

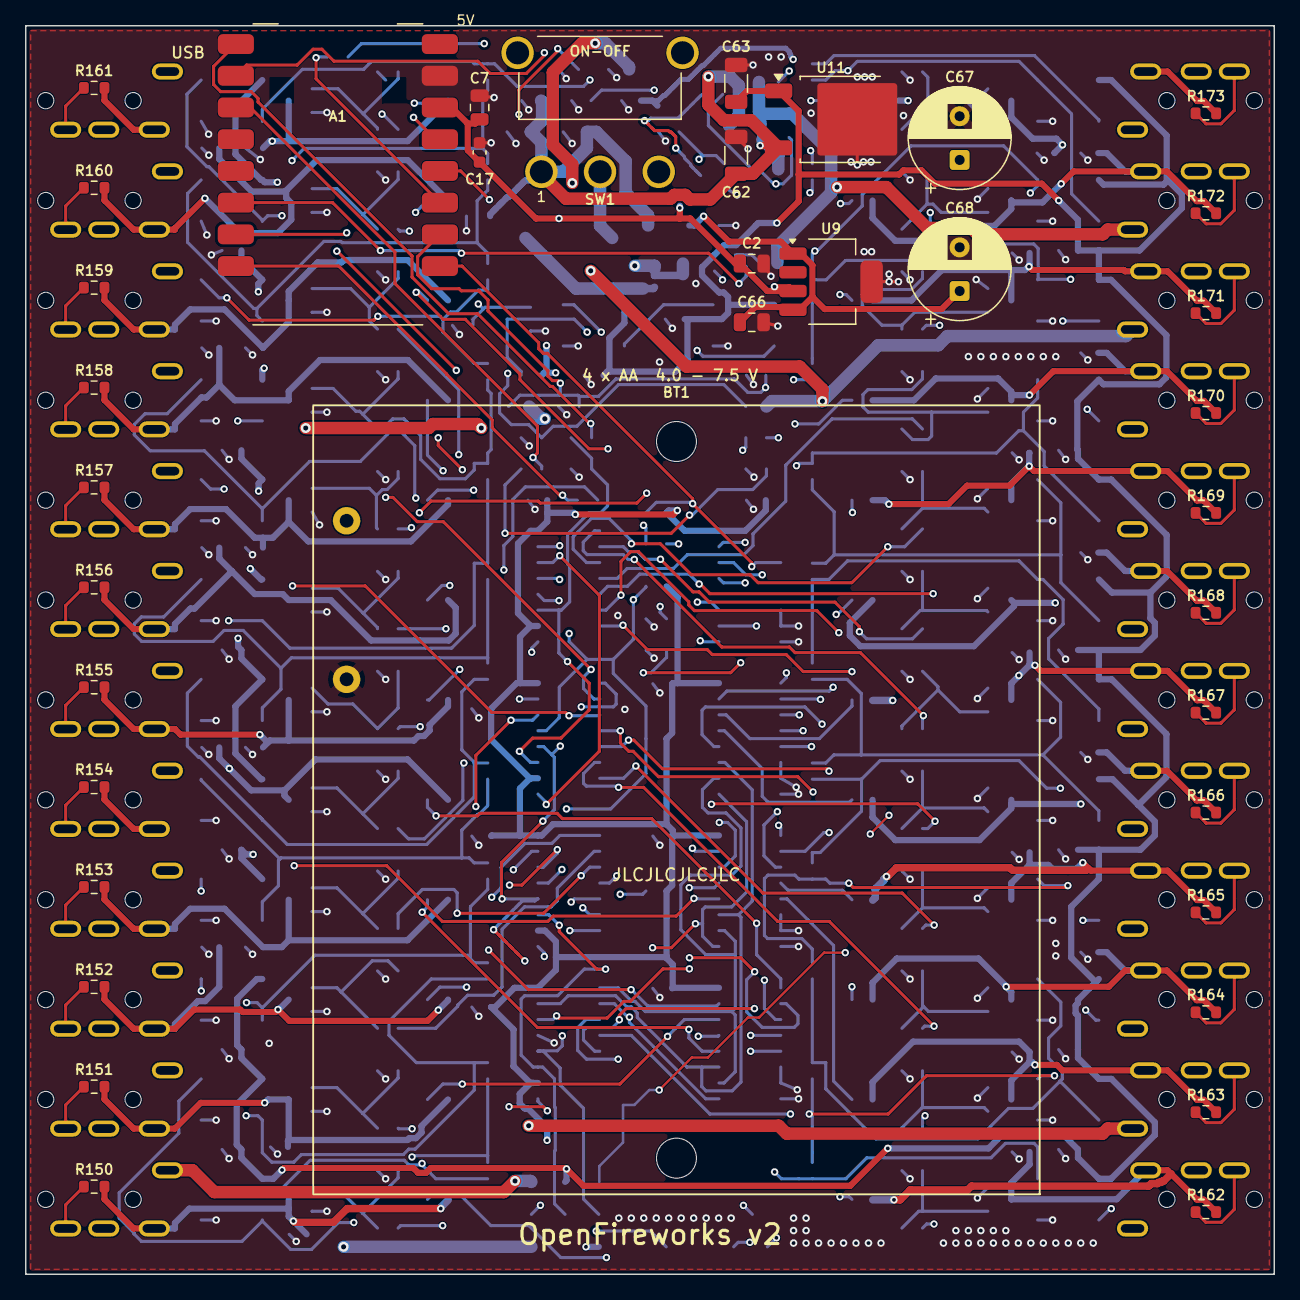
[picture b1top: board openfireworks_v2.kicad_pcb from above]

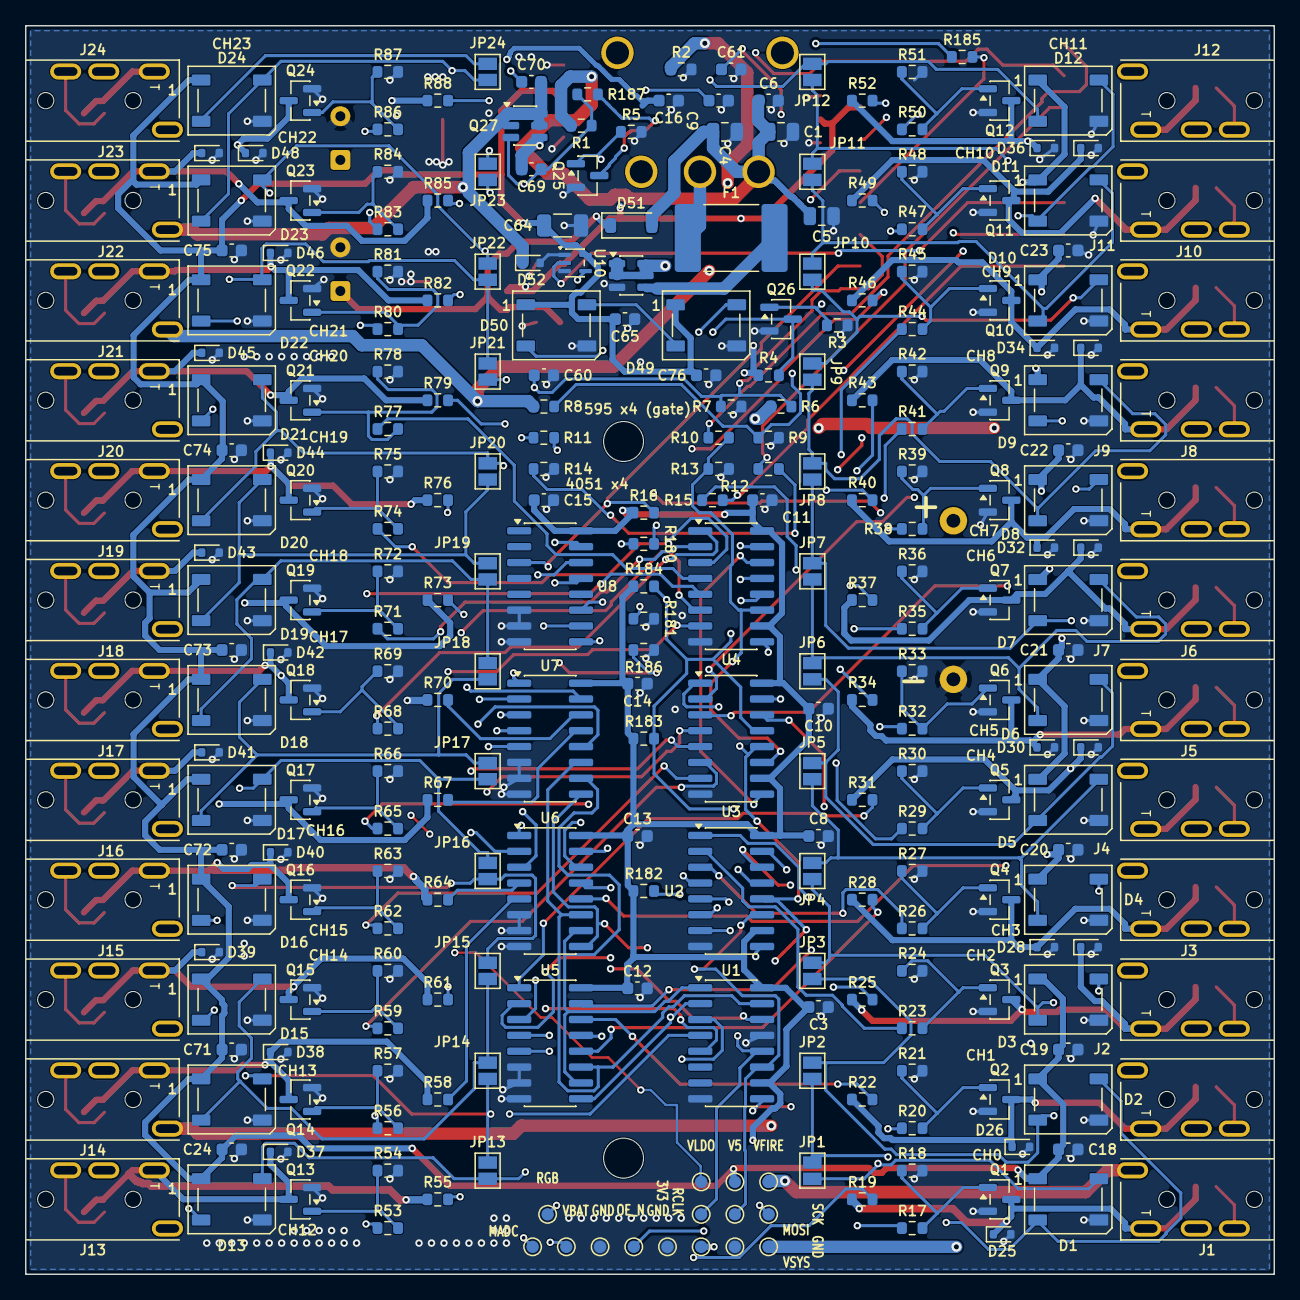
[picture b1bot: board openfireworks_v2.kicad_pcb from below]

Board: 4 copper layers, 100.0 x 100.0 mm, 319 parts (282 on the bottom side), 187 nets.

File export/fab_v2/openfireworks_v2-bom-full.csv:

Comment,Designator,Footprint,Qty,MPN
ESP32-C3 SuperMini,A1,ESP32C3_SuperMini_MINIV1,1,"ESP32-C3 SuperMini 'ESP32-C3 MINI V1' (DIY Mall; ESP32-C3FN4, ceramic antenna + U.FL, 18.0 x 23.8 mm)"
4xAA holder,BT1,BatteryHolder_Keystone_2477_4xAA,1,"Keystone 2477 (PC battery holder 4 x AA, THT, 58 x 63 x 16 mm)"
10uF,"C1,C2,C4,C5,C7,C66",C_0805_2012Metric,6,10uF 25V X5R 0805
100nF,"C3,C6,C8,C10,C11,C12,C13,C14,C15,C16,C17,C18,C19,C20,C21,C22,C23,C24,C65,C71,C72,C73,C74,C75,C76",C_0603_1608Metric,25,100nF 50V X7R 0603
10uF,"C62,C63,C64",C_1206_3216Metric,3,Samsung CL31B106KAHNNNF (10uF 25V X7R 1206)
470uF 10V,"C67,C68",CP_Radial_D8.0mm_P3.50mm,2,"Nichicon UPW1A471MPD (470 uF 10 V, low impedance 0.117 Ohm, D8 x 11.5, radial)"
220nF,C69,C_0603_1608Metric,1,220nF 25V X7R 0603
10nF,"C9,C60,C61,C70",C_0603_1608Metric,4,10nF 50V X7R 0603
WS2812B,"D1,D2,D3,D4,D5,D6,D7,D8,D9,D10,D11,D12,D13,D14,D15,D16,D17,D18,D19,D20,D21,D22,D23,D24,D49,D50",LED_WS2812B_PLCC4_5.0x5.0mm_P3.2mm,26,"WS2812B 5050 PLCC4 addressable RGB (5 V part: VDD 3.5-5.3 V, VIH 0.7 VDD, max 20 mA/colour); bought as Diamex 100563 '100 Stueck WS2812B LED RGB SMD 5050'"
ESD5Z12-AQ,"D25,D26,D27,D28,D29,D30,D31,D32,D33,D34,D35,D36,D37,D38,D39,D40,D41,D42,D43,D44,D45,D46,D47,D48,D52",D_SOD-523,25,"Diotec ESD5Z12-AQ (unidirectional ESD TVS, VWM 12 V, VBR >= 14.1 V, IR <= 0.01 uA @12 V, VCL 27 V @5 A, SOD-523; pin 1 = cathode band)"
1N5819HW,D51,D_SOD-123,1,"Diodes Inc 1N5819HW-7-F (Schottky 40 V 1 A, VF <= 0.45 V @ 1 A, SOD-123, cathode band)"
PPTC 1.5A hold,F1,Fuse_2920_7451Metric_Pad2.10x5.45mm_HandSolder,1,"Littelfuse 2920L150DR (PPTC 1.5 A hold, SMD 2920)"
PJ-320A,"J1,J2,J3,J4,J5,J6,J7,J8,J9,J10,J11,J12,J13,J14,J15,J16,J17,J18,J19,J20,J21,J22,J23,J24",Jack_35mm_PJ320A_THT,24,"PJ-320A 3.5 mm 4-pole jack, THT 4-pin, LONG pins (e.g. XKB PJ-320A, Shou Han PJ-320A-4P DIP, HCTL HC-PJ-320A-4P-D)"
JP_D0,JP1,SolderJumper-2_P1.3mm_Open_Pad1.0x1.5mm,1,"solder bridge (PCB copper, no bought part)"
JP_D1,JP2,SolderJumper-2_P1.3mm_Open_Pad1.0x1.5mm,1,"solder bridge (PCB copper, no bought part)"
JP_D2,JP3,SolderJumper-2_P1.3mm_Open_Pad1.0x1.5mm,1,"solder bridge (PCB copper, no bought part)"
JP_D3,JP4,SolderJumper-2_P1.3mm_Open_Pad1.0x1.5mm,1,"solder bridge (PCB copper, no bought part)"
JP_D4,JP5,SolderJumper-2_P1.3mm_Open_Pad1.0x1.5mm,1,"solder bridge (PCB copper, no bought part)"
JP_D5,JP6,SolderJumper-2_P1.3mm_Open_Pad1.0x1.5mm,1,"solder bridge (PCB copper, no bought part)"
JP_D6,JP7,SolderJumper-2_P1.3mm_Open_Pad1.0x1.5mm,1,"solder bridge (PCB copper, no bought part)"
JP_D7,JP8,SolderJumper-2_P1.3mm_Open_Pad1.0x1.5mm,1,"solder bridge (PCB copper, no bought part)"
JP_D8,JP9,SolderJumper-2_P1.3mm_Open_Pad1.0x1.5mm,1,"solder bridge (PCB copper, no bought part)"
JP_D9,JP10,SolderJumper-2_P1.3mm_Open_Pad1.0x1.5mm,1,"solder bridge (PCB copper, no bought part)"
JP_D10,JP11,SolderJumper-2_P1.3mm_Open_Pad1.0x1.5mm,1,"solder bridge (PCB copper, no bought part)"
JP_D11,JP12,SolderJumper-2_P1.3mm_Open_Pad1.0x1.5mm,1,"solder bridge (PCB copper, no bought part)"
JP_D12,JP13,SolderJumper-2_P1.3mm_Open_Pad1.0x1.5mm,1,"solder bridge (PCB copper, no bought part)"
JP_D13,JP14,SolderJumper-2_P1.3mm_Open_Pad1.0x1.5mm,1,"solder bridge (PCB copper, no bought part)"
JP_D14,JP15,SolderJumper-2_P1.3mm_Open_Pad1.0x1.5mm,1,"solder bridge (PCB copper, no bought part)"
JP_D15,JP16,SolderJumper-2_P1.3mm_Open_Pad1.0x1.5mm,1,"solder bridge (PCB copper, no bought part)"
JP_D16,JP17,SolderJumper-2_P1.3mm_Open_Pad1.0x1.5mm,1,"solder bridge (PCB copper, no bought part)"
JP_D17,JP18,SolderJumper-2_P1.3mm_Open_Pad1.0x1.5mm,1,"solder bridge (PCB copper, no bought part)"
JP_D18,JP19,SolderJumper-2_P1.3mm_Open_Pad1.0x1.5mm,1,"solder bridge (PCB copper, no bought part)"
JP_D19,JP20,SolderJumper-2_P1.3mm_Open_Pad1.0x1.5mm,1,"solder bridge (PCB copper, no bought part)"
JP_D20,JP21,SolderJumper-2_P1.3mm_Open_Pad1.0x1.5mm,1,"solder bridge (PCB copper, no bought part)"
JP_D21,JP22,SolderJumper-2_P1.3mm_Open_Pad1.0x1.5mm,1,"solder bridge (PCB copper, no bought part)"
JP_D22,JP23,SolderJumper-2_P1.3mm_Open_Pad1.0x1.5mm,1,"solder bridge (PCB copper, no bought part)"
JP_D23,JP24,SolderJumper-2_P1.3mm_Open_Pad1.0x1.5mm,1,"solder bridge (PCB copper, no bought part)"
AO3400 (low-side),"Q1,Q2,Q3,Q4,Q5,Q6,Q7,Q8,Q9,Q10,Q11,Q12,Q13,Q14,Q15,Q16,Q17,Q18,Q19,Q20,Q21,Q22,Q23,Q24",SOT-23,24,"AO3400 class N-FET, SOT-23 G1/S2/D3: AOS AO3400 / AO3400A or Yangjie YJL3400A (30 V, Vgs(th) <= 1.5 V, RDS(on) <= 52 mOhm @ 2.5 V, IDM >= 23 A)"
AO3400 (arm driver),"Q25,Q26",SOT-23,2,"AO3400 class N-FET, SOT-23 G1/S2/D3 (same part as Q1-Q24: AOS AO3400/AO3400A or Yangjie YJL3400A; Vgs(th) 0.65-1.45 V, RDS(on) specified at 2.5 V)"
DMP2035UVT (ARM rail),Q27,TSOT-23-6,1,"Diodes DMP2035UVT-7 (P-FET -20 V, VGS +-12 V, Vgs(th) -0.4..-1.5 V, RDS(on) <= 35 mOhm @-4.5 V / 45 @-2.5 V / 62 @-1.8 V, IDM -24 A, TSOT-26: D 1,2,5,6 / G 3 / S 4)"
DMP2035UVT (reverse block),Q28,TSOT-23-6,1,"Diodes DMP2035UVT-7 (P-FET -20 V, VGS +-12 V, RDS(on) <= 35 mOhm @-4.5 V / 45 @-2.5 V, IDM -24 A, TSOT-26: D 1,2,5,6 / G 3 / S 4)"
2.2k,"R3,R5",R_0603_1608Metric,2,any 2.2k 0603 1%
220k,"R6,R8",R_0603_1608Metric,2,any 220k 0603 1%
33R,"R10,R11,R12,R180",R_0603_1608Metric,4,any 33R 0603
150R,"R17,R20,R23,R26,R29,R32,R35,R38,R41,R44,R47,R50,R53,R56,R59,R62,R65,R68,R71,R74,R77,R80,R83,R86",R_0603_1608Metric,24,any 150R 0603
47k,"R2,R19,R22,R25,R28,R31,R34,R37,R40,R43,R46,R49,R52,R55,R58,R61,R64,R67,R70,R73,R76,R79,R82,R85,R88",R_0603_1608Metric,25,any 47k 0603 1%
100k,"R7,R9,R16,R18,R21,R24,R27,R30,R33,R36,R39,R42,R45,R48,R51,R54,R57,R60,R63,R66,R69,R72,R75,R78,R81,R84,R87,R150,R151,R152,R153,R154,R155,R156,R157,R158,R159,R160,R161,R162,R163,R164,R165,R166,R167,R168,R169,R170,R171,R172,R173,R181",R_0603_1608Metric,52,any 100k 0603 1%
10k,"R1,R4,R13,R14,R15,R182,R183,R184,R185,R186",R_0603_1608Metric,10,any 10k 0603 1%
1k,R187,R_0603_1608Metric,1,any 1k 0603 1%
5MS1S102AM6QE,SW1,Switch_Slide_LightCountry_5MS1_M6,1,"Light Country 5MS1S102AM6QE (SPDT ON-ON, right-angle PCB M6, S1 actuator, 2A/250VAC 5A/28VDC)"
VSYS,TP1,TestPoint_Pad_D1.0mm,1,test pad (PCB copper)
GND,TP2,TestPoint_Pad_D1.0mm,1,test pad (PCB copper)
3V3,TP3,TestPoint_Pad_D1.0mm,1,test pad (PCB copper)
GND2,TP4,TestPoint_Pad_D1.0mm,1,test pad (PCB copper)
GATE_OE_N,TP5,TestPoint_Pad_D1.0mm,1,test pad (PCB copper)
GND3,TP6,TestPoint_Pad_D1.0mm,1,test pad (PCB copper)
VBAT_DIV,TP7,TestPoint_Pad_D1.0mm,1,test pad (PCB copper)
MUX_ADC,TP8,TestPoint_Pad_D1.0mm,1,test pad (PCB copper)
MOSI,TP9,TestPoint_Pad_D1.0mm,1,test pad (PCB copper)
SCK,TP10,TestPoint_Pad_D1.0mm,1,test pad (PCB copper)
RCLK,TP11,TestPoint_Pad_D1.0mm,1,test pad (PCB copper)
RGB_DATA,TP12,TestPoint_Pad_D1.0mm,1,test pad (PCB copper)
VFIRE,TP13,TestPoint_Pad_D1.0mm,1,test pad (PCB copper)
V5_LED,TP14,TestPoint_Pad_D1.0mm,1,test pad (PCB copper)
VLDO,TP15,TestPoint_Pad_D1.0mm,1,test pad (PCB copper)
74HC595,"U1,U2,U3,U4",SOIC-16_3.9x9.9mm_P1.27mm,4,"SN74HC595D (8-bit shift register, SOIC-16)"
74HC4051D,"U5,U6,U7,U8",SOIC-16_3.9x9.9mm_P1.27mm,4,"Toshiba 74HC4051D(BJ) (8:1 analog mux, specified from 2 V, SOIC-16; pin-compatible with CD4051)"
LP38692MP-3.3,U9,SOT-223-5,1,"TI LP38692MP-3.3/NOPB (1 A LDO, VIN 2.7-10 V, abs max 12 V, SOT-223-5: 1 EN, 2 NC, 3 OUT, 4 IN, 5 GND tab)"
SN74LV1T125DCKR,U10,SOT-353_SC-70-5,1,"TI SN74LV1T125DCKR (single buffer with level-shifting inputs, VCC 1.6-5.5 V, SC-70-5 / DCK; pinout = 74AHCT1G125: 1 OE#, 2 A, 3 GND, 4 Y, 5 VCC)"
LP38691DTX-5.0,U11,TO-252-2,1,"TI LP38691DTX-5.0/NOPB (500 mA LDO, VIN 2.7-10 V, TO-252: 1 OUT, tab GND, 3 IN)"
